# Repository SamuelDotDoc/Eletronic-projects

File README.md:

# Eletronic-projects
Repositório para estudos de Eletrônica e Design de PCB

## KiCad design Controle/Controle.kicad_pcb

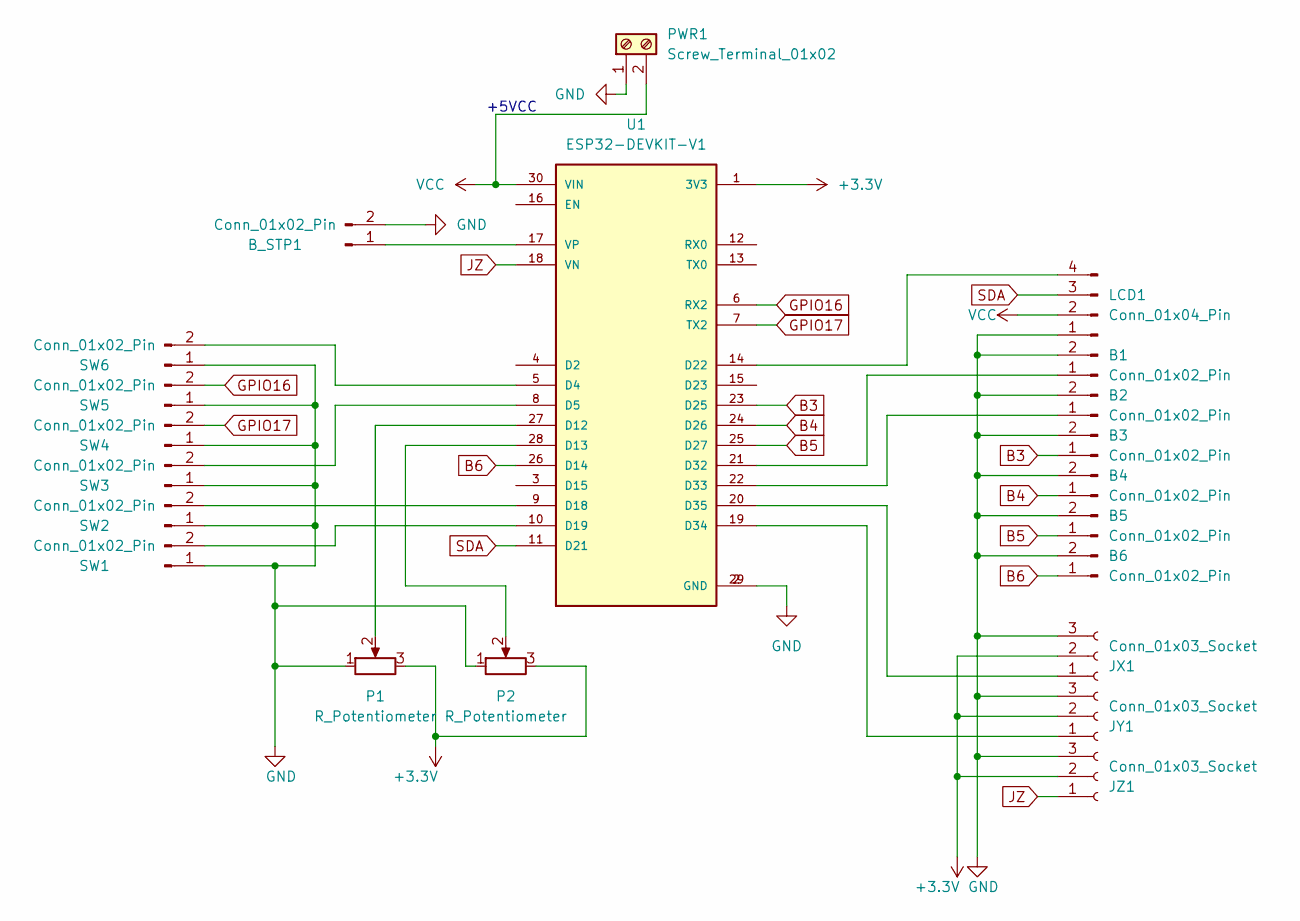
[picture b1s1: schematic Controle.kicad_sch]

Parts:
B1, B2, B3, B4, B5, B6: Conn_01x02_Pin; PinHeader_1x02_P2.54mm_Vertical
B_STP1: Conn_01x02_Pin; PinHeader_1x02_P2.54mm_Vertical
JX1: Conn_01x03_Socket; PinSocket_1x03_P2.54mm_Vertical
JY1: Conn_01x03_Socket; PinSocket_1x03_P2.54mm_Vertical
JZ1: Conn_01x03_Socket; PinSocket_1x03_P2.54mm_Vertical
LCD1: Conn_01x04_Pin; PinHeader_1x04_P2.54mm_Vertical
P1, P2: R_Potentiometer; Potentiometer_Alps_RK09Y11_Single_Horizontal
PWR1: Screw_Terminal_01x02; TerminalBlock_bornier-2_P5.08mm
SW1, SW2, SW3, SW4, SW5, SW6: Conn_01x02_Pin; PinHeader_1x02_P2.54mm_Vertical
U1: ESP32-DEVKIT-V1; MODULE_ESP32_DEVKIT_V1; PARTREV N/A

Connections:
+3.3V: JX1.2, JY1.2, JZ1.2, P1.3, P2.3, U1.1 (3V3)
B3: B3.1, U1.23 (D25)
B4: B4.1, U1.24 (D26)
B5: B5.1, U1.25 (D27)
B6: B6.1, U1.26 (D14)
GND: B1.2, B2.2, B3.2, B4.2, B5.2, B6.2, B_STP1.2, JX1.3, JY1.3, JZ1.3, LCD1.1, P1.1, P2.1, PWR1.1, SW1.1, SW2.1, SW3.1, SW4.1, SW5.1, SW6.1, U1.2 (GND), U1.29 (GND); also elsewhere on the board
GPIO16: SW5.2, U1.6 (RX2)
GPIO17: SW4.2, U1.7 (TX2)
JZ: JZ1.1, U1.18 (VN)
unnamed: B1.1, U1.21 (D32)
unnamed: B2.1, U1.22 (D33)
unnamed: B_STP1.1, U1.17 (VP)
unnamed: JX1.1, U1.20 (D35)
unnamed: JY1.1, U1.19 (D34)
unnamed: LCD1.4, U1.14 (D22)
unnamed: SW1.2, U1.10 (D19)
unnamed: SW2.2, U1.9 (D18)
unnamed: SW3.2, U1.8 (D5)
unnamed: SW6.2, U1.5 (D4)
unnamed: P1.2, U1.27 (D12)
unnamed: P2.2, U1.28 (D13)
SDA: LCD1.3, U1.11 (D21)
VCC: LCD1.2, PWR1.2, U1.30 (VIN); also elsewhere on the board

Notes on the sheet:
+5VCC

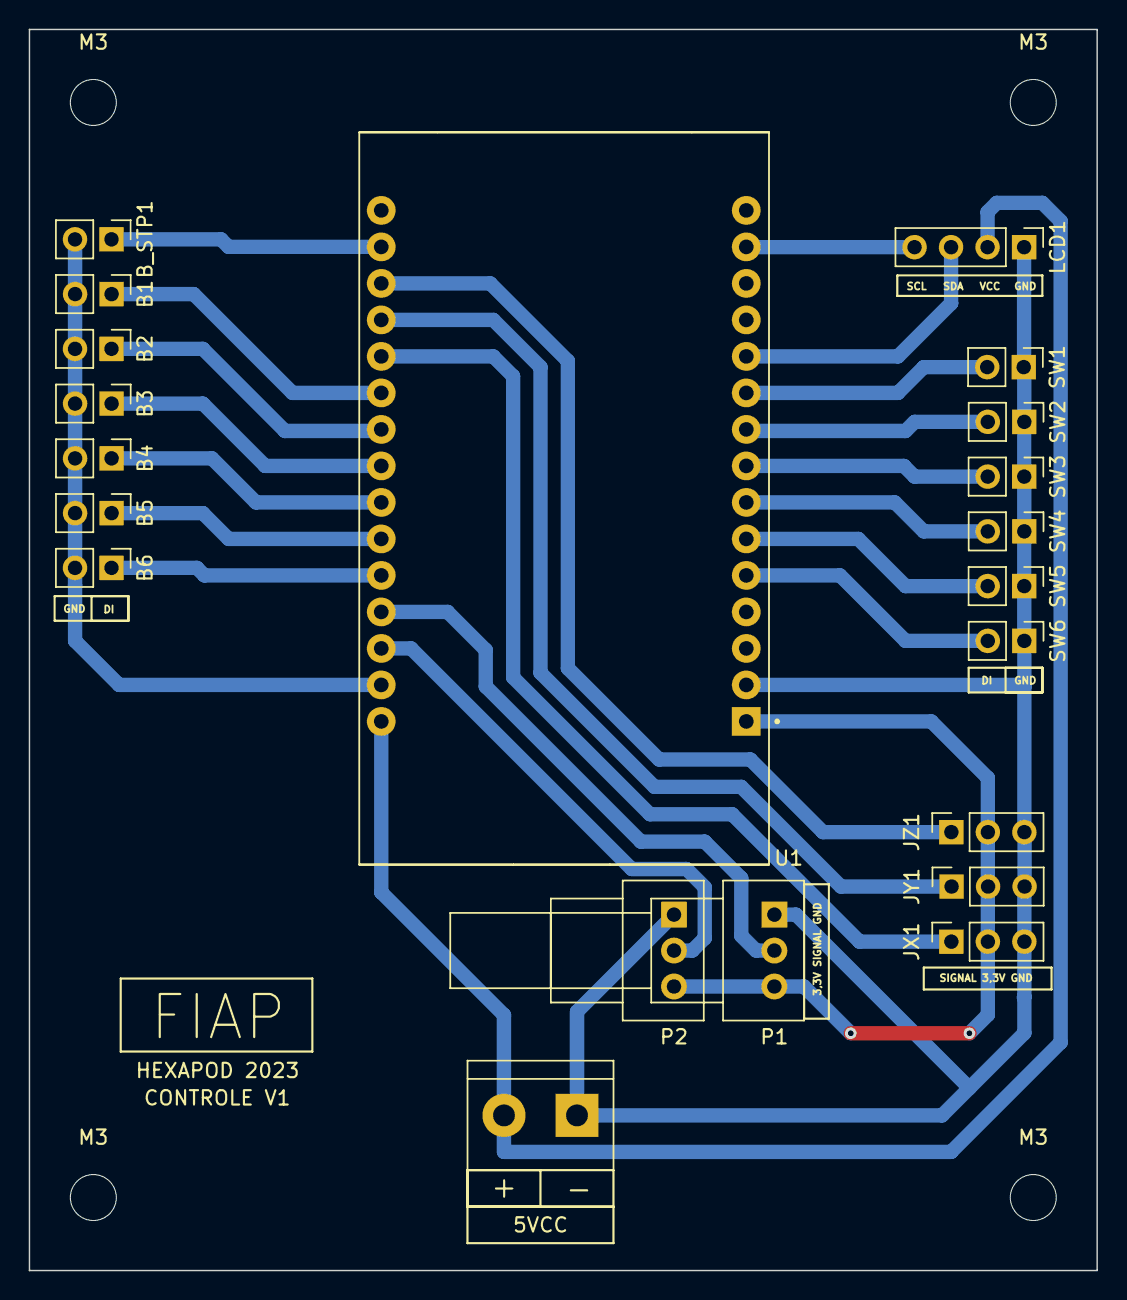
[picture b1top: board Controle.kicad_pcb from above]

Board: 2 copper layers, 74.3 x 86.4 mm, 25 parts (0 on the bottom side), 23 nets.

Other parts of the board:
5VCC: Screw_Terminal_01x02; TerminalBlock_bornier-2_P5.08mm
M3, M3#2, M3#3, M3#4: MountingHole_3.2mm_M3

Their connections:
GND: 5VCC.1; also elsewhere on the board
VCC: 5VCC.2; also elsewhere on the board

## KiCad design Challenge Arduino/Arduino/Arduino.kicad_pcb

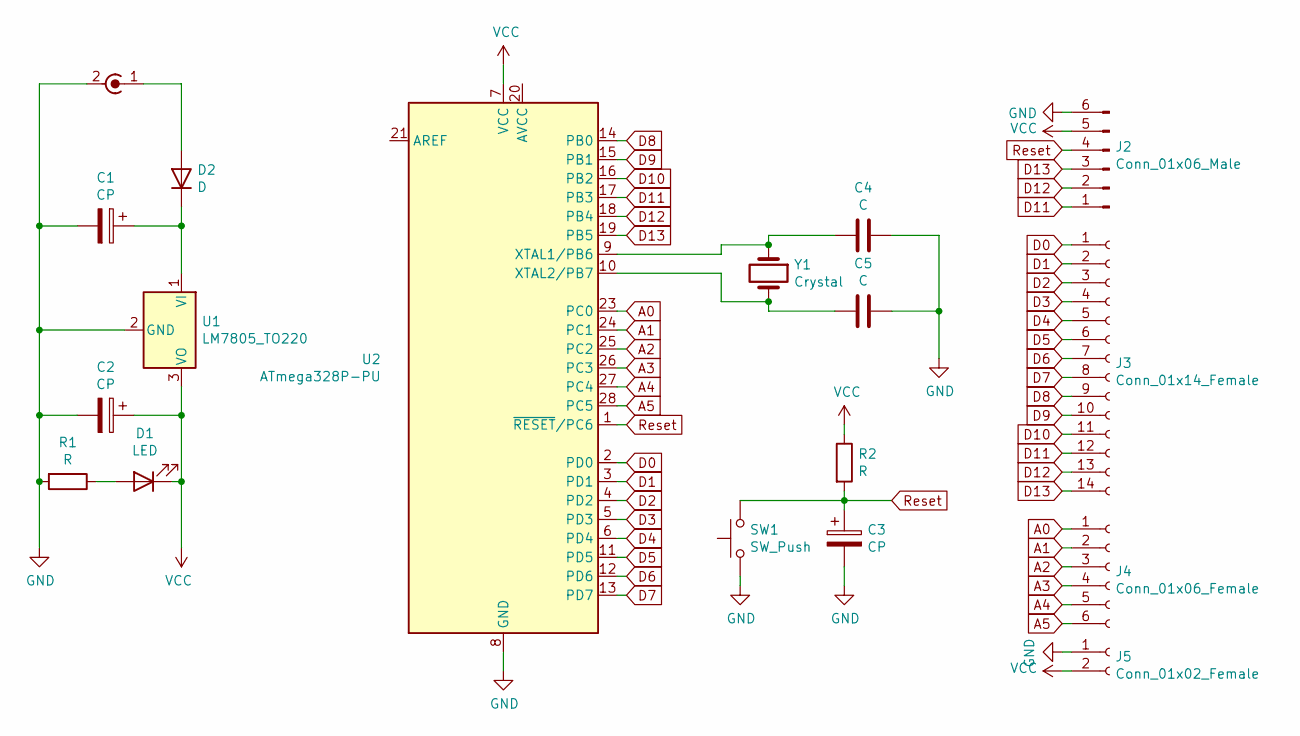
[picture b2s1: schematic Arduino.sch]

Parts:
C1, C2, C3: CP; CP_Radial_D5.0mm_P2.50mm
C4, C5: C; C_Disc_D4.3mm_W1.9mm_P5.00mm
D1: LED; LED_D3.0mm
D2: D; D_DO-41_SOD81_P10.16mm_Horizontal
J1: Conn_Coaxial_Power; BarrelJack_Horizontal
J2: Conn_01x06_Male; PinHeader_1x06_P2.54mm_Vertical
J3: Conn_01x14_Female; PinSocket_1x14_P2.54mm_Vertical
J4: Conn_01x06_Female; PinSocket_1x06_P2.54mm_Vertical
J5: Conn_01x02_Female; PinSocket_1x02_P2.54mm_Vertical
R1, R2: R; R_Axial_DIN0207_L6.3mm_D2.5mm_P10.16mm_Horizontal
SW1: SW_Push; SW_PUSH_6mm
U1: LM7805_TO220; TO-220-3_Vertical
U2: ATmega328P-PU; DIP-28_W7.62mm
Y1: Crystal; Crystal_HC49-4H_Vertical

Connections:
A0: J4.1, U2.23 (PC0)
A1: J4.2, U2.24 (PC1)
A2: J4.3, U2.25 (PC2)
A3: J4.4, U2.26 (PC3)
A4: J4.5, U2.27 (PC4)
A5: J4.6, U2.28 (PC5)
D0: J3.1, U2.2 (PD0)
D1: J3.2, U2.3 (PD1)
D2: J3.3, U2.4 (PD2)
D3: J3.4, U2.5 (PD3)
D4: J3.5, U2.6 (PD4)
D5: J3.6, U2.11 (PD5)
D6: J3.7, U2.12 (PD6)
D7: J3.8, U2.13 (PD7)
D8: J3.9, U2.14 (PB0)
D9: J3.10, U2.15 (PB1)
D10: J3.11, U2.16 (PB2)
D11: J2.1, J3.12, U2.17 (PB3)
D12: J2.2, J3.13, U2.18 (PB4)
D13: J2.3, J3.14, U2.19 (PB5)
GND: C1.2, C2.2, C3.2, C4.1, C5.1, J1.2 (Ext), J2.6, J5.1, R1.2, SW1.1, U1.2 (GND), U2.8 (GND), U2.22 (GND)
unnamed: C1.1, D2.1 (K), U1.1 (VI)
unnamed: C4.2, U2.9 (XTAL1/PB6), Y1.1
unnamed: C5.2, U2.10 (XTAL2/PB7), Y1.2
unnamed: D1.2 (A), R1.1
unnamed: D2.2 (A), J1.1 (In)
Reset: C3.1, J2.4, R2.2, SW1.2, U2.1 (~RESET~/PC6)
VCC: C2.1, D1.1 (K), J2.5, J5.2, R2.1, U1.3 (VO), U2.7 (VCC)

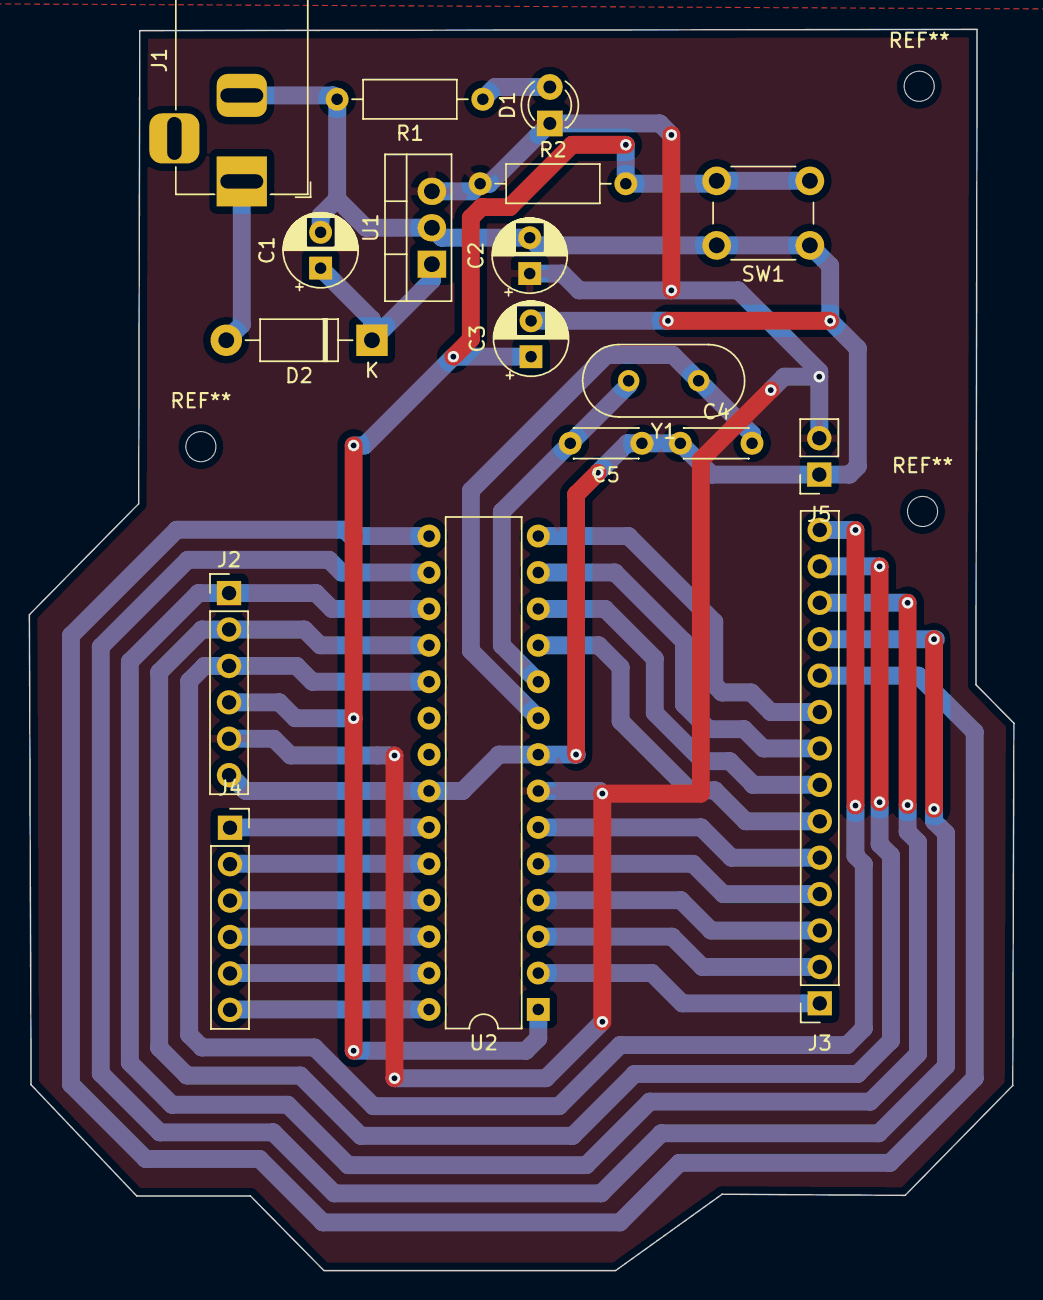
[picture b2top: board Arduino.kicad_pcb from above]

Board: 2 copper layers, 68.7 x 86.6 mm, 18 parts (0 on the bottom side), 28 nets.

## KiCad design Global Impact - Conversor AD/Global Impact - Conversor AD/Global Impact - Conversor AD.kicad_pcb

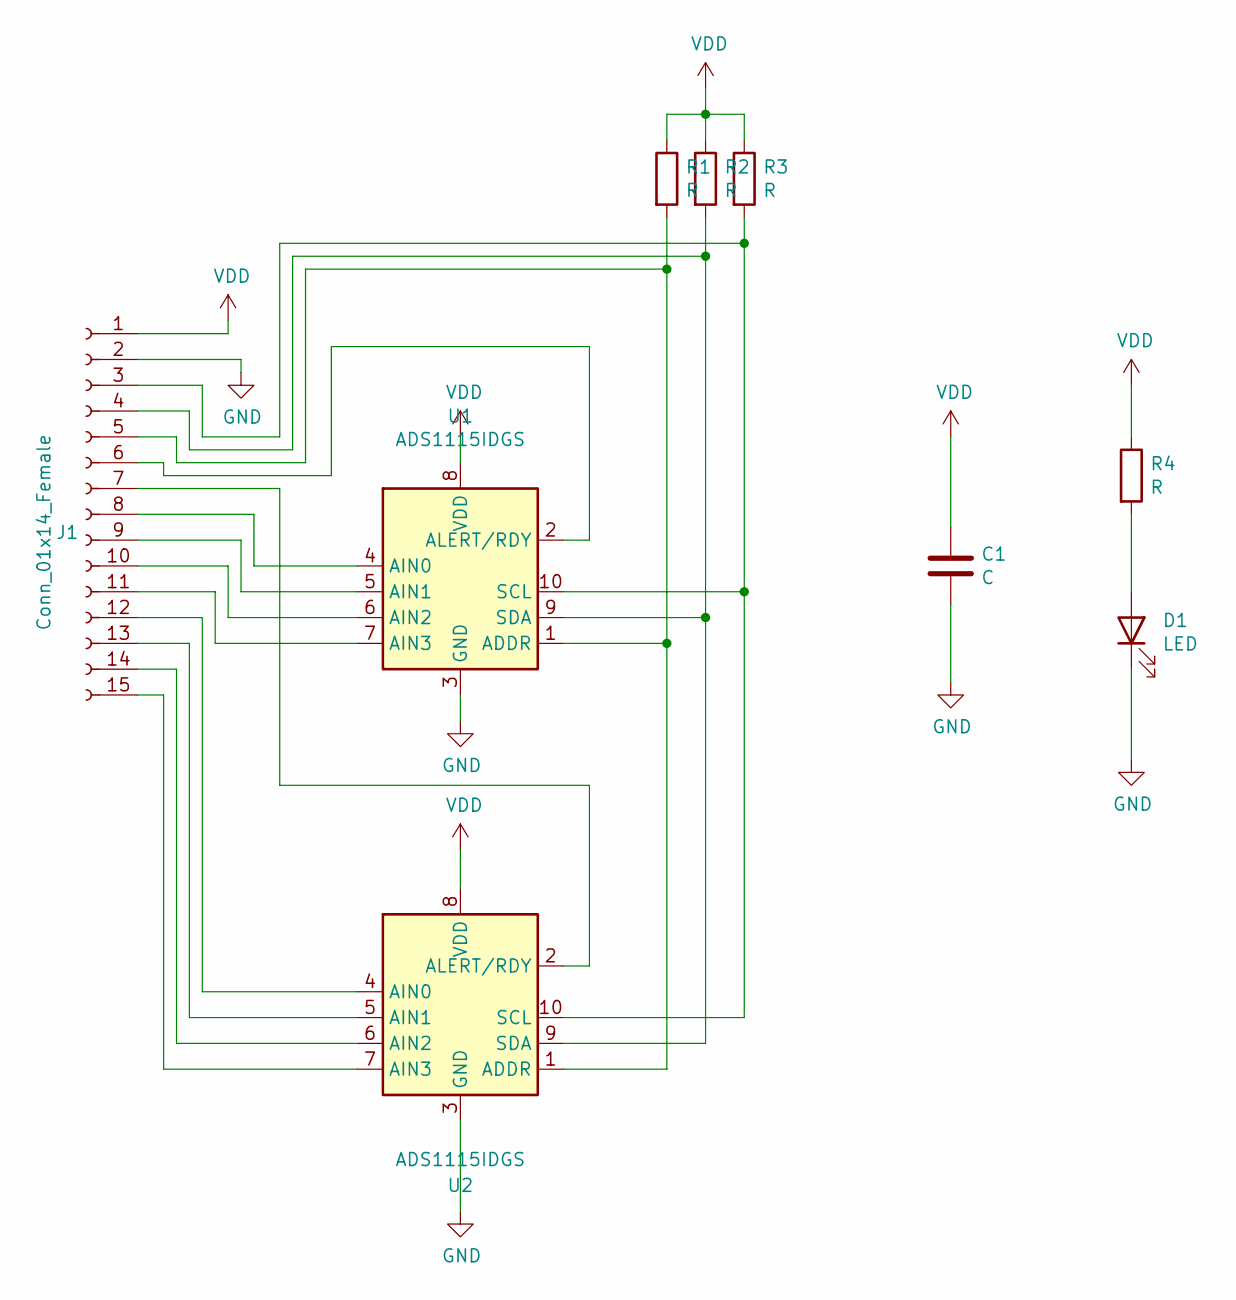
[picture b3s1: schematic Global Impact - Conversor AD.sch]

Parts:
C1: C; C_0805_2012Metric
D1: LED; LED_D3.0mm
J1: Conn_01x14_Female; PinSocket_1x15_P2.54mm_Vertical
R1, R2, R3, R4: R; R_1206_3216Metric
U1, U2: ADS1115IDGS; TSSOP-10_3x3mm_P0.5mm

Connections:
GND: C1.2, D1.1 (K), J1.2, U1.3 (GND), U2.3 (GND)
unnamed: D1.2 (A), R4.2
unnamed: J1.3, R3.2, U1.10 (SCL), U2.10 (SCL)
unnamed: J1.4, R2.2, U1.9 (SDA), U2.9 (SDA)
unnamed: J1.5, R1.2, U1.1 (ADDR), U2.1 (ADDR)
unnamed: J1.6, U1.2 (ALERT/RDY)
unnamed: J1.7, U2.2 (ALERT/RDY)
unnamed: J1.8, U1.4 (AIN0)
unnamed: J1.9, U1.5 (AIN1)
unnamed: J1.10, U1.6 (AIN2)
unnamed: J1.11, U1.7 (AIN3)
unnamed: J1.12, U2.4 (AIN0)
unnamed: J1.13, U2.5 (AIN1)
unnamed: J1.14, U2.6 (AIN2)
unnamed: J1.15, U2.7 (AIN3)
VDD: C1.1, J1.1, R1.1, R2.1, R3.1, R4.1, U1.8 (VDD), U2.8 (VDD)

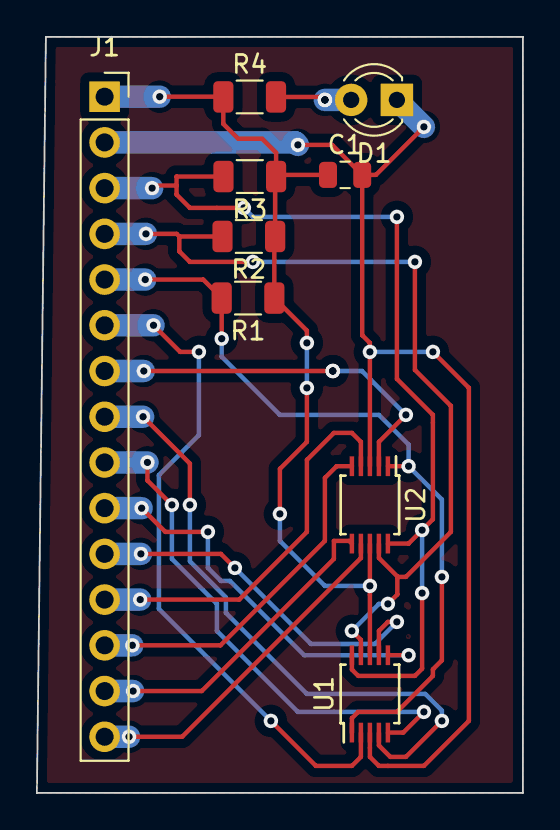
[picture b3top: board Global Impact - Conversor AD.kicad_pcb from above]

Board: 2 copper layers, 27.0 x 42.0 mm, 9 parts (0 on the bottom side), 16 nets.

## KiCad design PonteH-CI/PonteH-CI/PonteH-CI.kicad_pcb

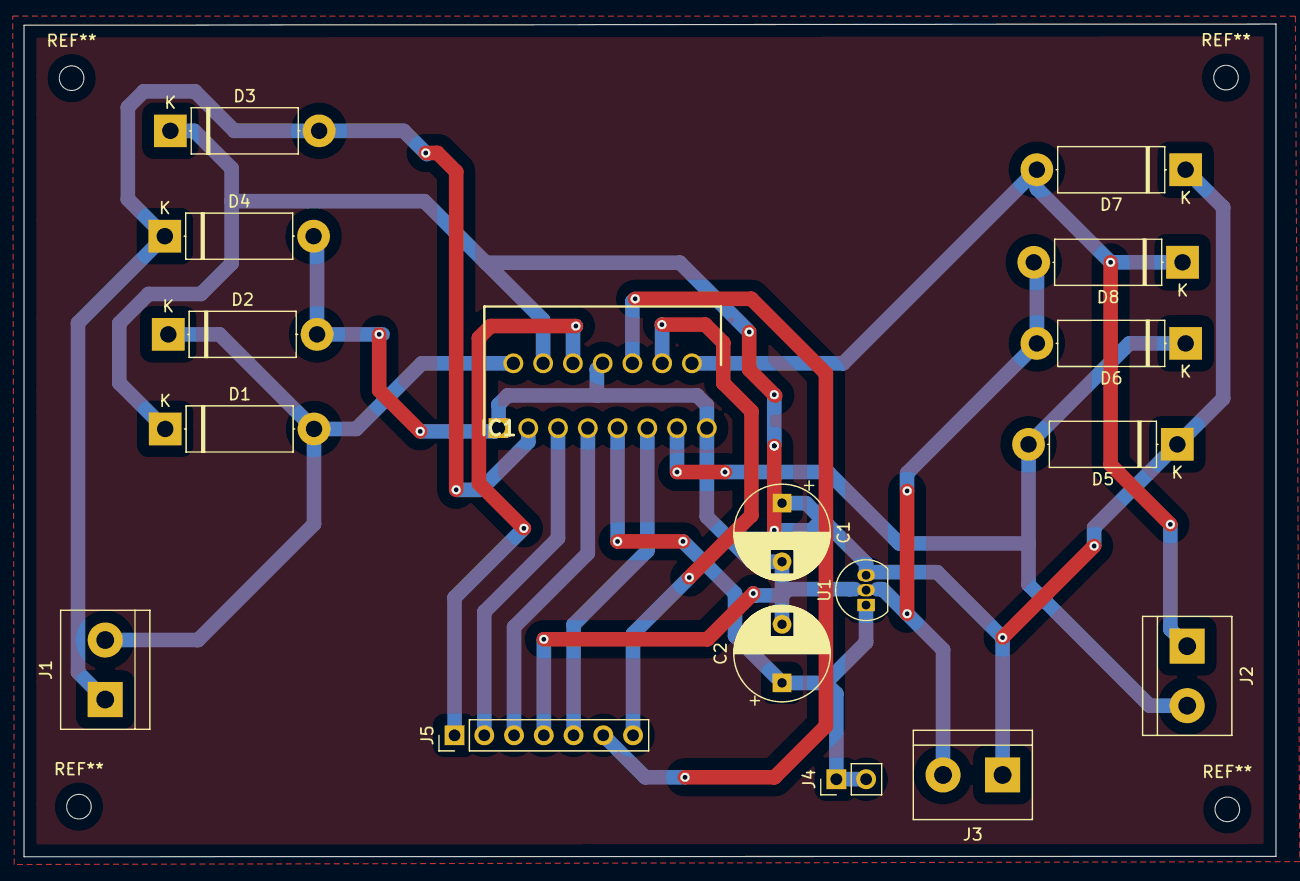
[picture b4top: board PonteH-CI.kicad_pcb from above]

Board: 2 copper layers, 106.9 x 71.1 mm, 17 parts (0 on the bottom side), 13 nets.

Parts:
C1, C2: CP; CP_Radial_D8.0mm_P5.00mm
D1, D2, D3, D4, D5, D6, D7, D8: D; D_5W_P12.70mm_Horizontal
IC1: L298N; TO127P500X2020X2210-15P
J1, J2, J3: Screw_Terminal_01x02; TerminalBlock_bornier-2_P5.08mm
J4: Conn_01x02_Male; PinHeader_1x02_P2.54mm_Vertical
J5: Conn_01x07_Male; PinHeader_1x07_P2.54mm_Vertical
U1: L78L05_TO92; TO-92_Inline

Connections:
+5V: C2.1, IC1.9, J4.1, J4.2, U1.1
EnableA: IC1.6, J5.1
EnableB: IC1.11, J5.5
GND: C1.2, C2.2, D2.2, D4.2, D6.2, D8.2, IC1.1, IC1.8, IC1.15, J3.2, J5.4, U1.2
Input1: IC1.5, J5.2
Input2: IC1.7, J5.3
Input3: IC1.10, J5.6
Input4: IC1.12, J5.7
Output1: D1.2, D2.1, IC1.2, J1.2
Output2: D3.2, D4.1, IC1.3, J1.1
Output3: D5.2, D6.1, IC1.13, J2.2
Output4: D7.2, D8.1, IC1.14, J2.1
VD: C1.1, D1.1, D3.1, D5.1, D7.1, IC1.4, J3.1, U1.3

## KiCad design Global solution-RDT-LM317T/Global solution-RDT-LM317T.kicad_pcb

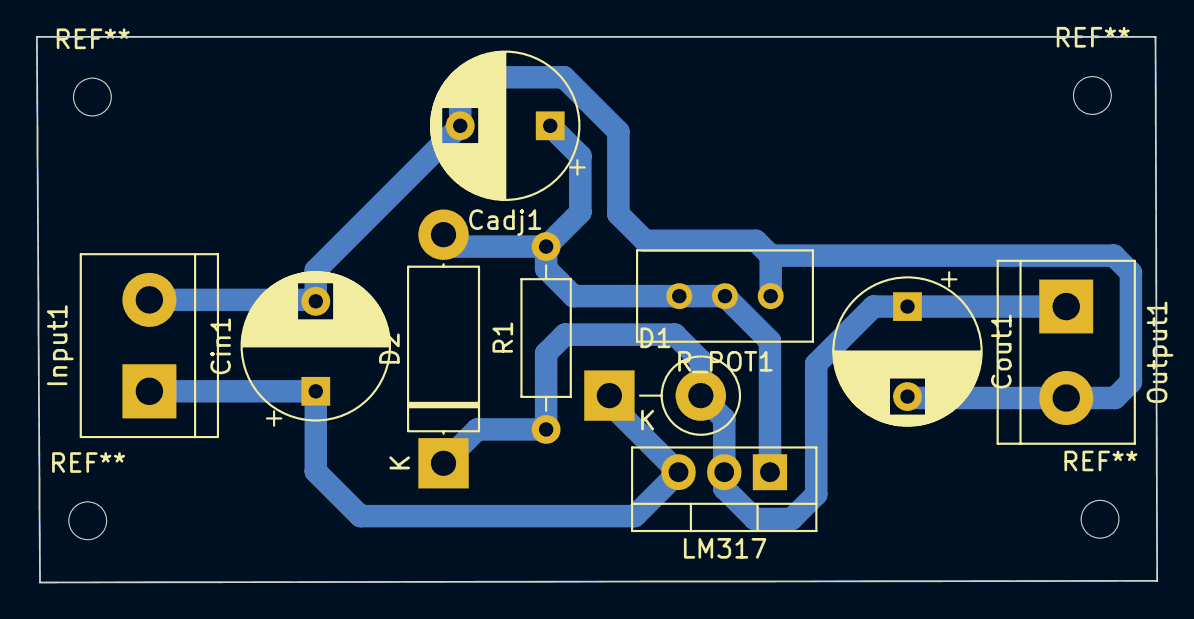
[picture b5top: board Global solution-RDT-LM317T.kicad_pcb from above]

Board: 2 copper layers, 62.2 x 30.3 mm, 10 parts (0 on the bottom side), 4 nets.

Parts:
Cadj1: 47uF; CP_Radial_D8.0mm_P5.00mm
Cin1: 100uF; CP_Radial_D8.0mm_P5.00mm
Cout1: 47uF; CP_Radial_D8.0mm_P5.00mm
D1: 1N4007; D_5W_P5.08mm_Vertical_KathodeUp
D2: 1N4007; D_5W_P12.70mm_Horizontal
Input1: Screw_Terminal_01x02; TerminalBlock_bornier-2_P5.08mm
LM317: LM317_3PinPackage; TO-220-3_Vertical
Output1: Screw_Terminal_01x02; TerminalBlock_bornier-2_P5.08mm
R1: 430R; R_Axial_DIN0207_L6.3mm_D2.5mm_P10.16mm_Horizontal
R_POT1: 10K; Potentiometer_Bourns_3296W_Vertical

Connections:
GND: Cadj1.2, Cin1.2, Cout1.2, Input1.2, Output1.2, R_POT1.3
unnamed: Cadj1.1, D2.2, LM317.1, R1.2, R_POT1.1, R_POT1.2
unnamed: Cin1.1, D1.1, Input1.1, LM317.3
unnamed: Cout1.1, D1.2, D2.1, LM317.2, Output1.1, R1.1

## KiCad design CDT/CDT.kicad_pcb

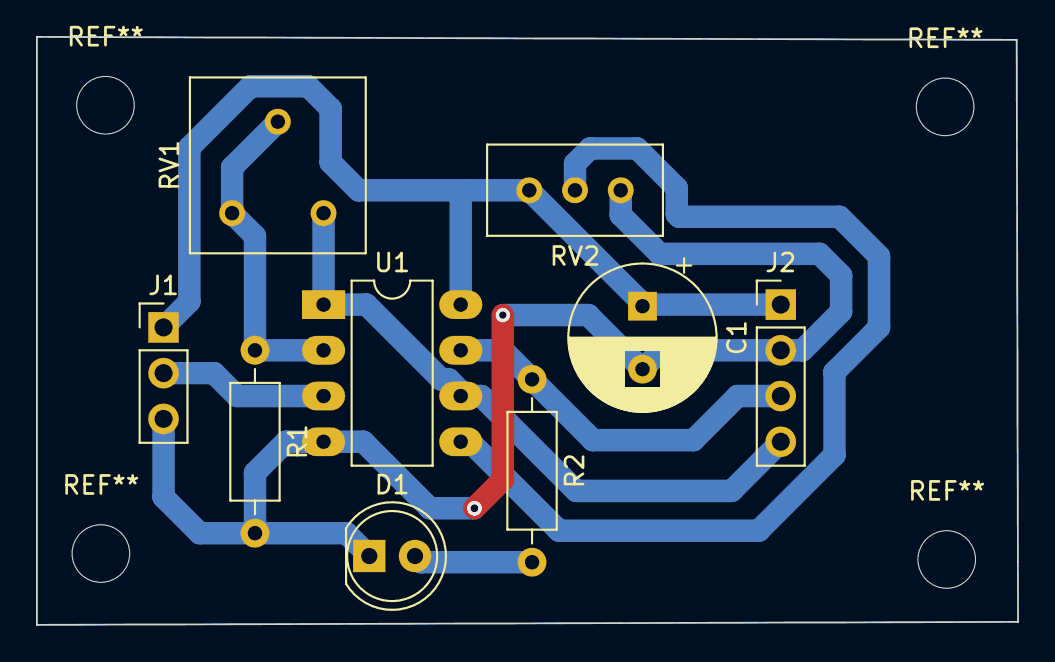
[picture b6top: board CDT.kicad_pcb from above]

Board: 2 copper layers, 54.5 x 32.7 mm, 9 parts (0 on the bottom side), 8 nets.

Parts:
C1: CP; CP_Radial_D8.0mm_P3.50mm
D1: LED; LED_D5.0mm
J1: Conn_01x03_Male; PinHeader_1x03_P2.54mm_Vertical
J2: Conn_01x04_Male; PinHeader_1x04_P2.54mm_Vertical
R1, R2: R; R_Axial_DIN0207_L6.3mm_D2.5mm_P10.16mm_Horizontal
RV1: R_POT; Potentiometer_Bourns_3386F_Vertical
RV2: R_POT; Potentiometer_Bourns_3296W_Vertical
U1: LM358; DIP-8_W7.62mm_LongPads

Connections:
GND: C1.2, D1.1, J1.3, J2.2, R1.2, RV2.3, U1.4
unnamed: D1.2, R2.2
unnamed: J1.2, U1.3
unnamed: R1.1, RV1.2, RV1.3, U1.2
unnamed: RV2.2, U1.5
VCC: C1.1, J1.1, J2.1, RV2.1, U1.8
VG10: J2.4, RV1.1, U1.1, U1.6
Vout(D): J2.3, R2.1, U1.7

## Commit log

2023-11-15 Adding projects to Git
2023-11-15 Adding project Controle
